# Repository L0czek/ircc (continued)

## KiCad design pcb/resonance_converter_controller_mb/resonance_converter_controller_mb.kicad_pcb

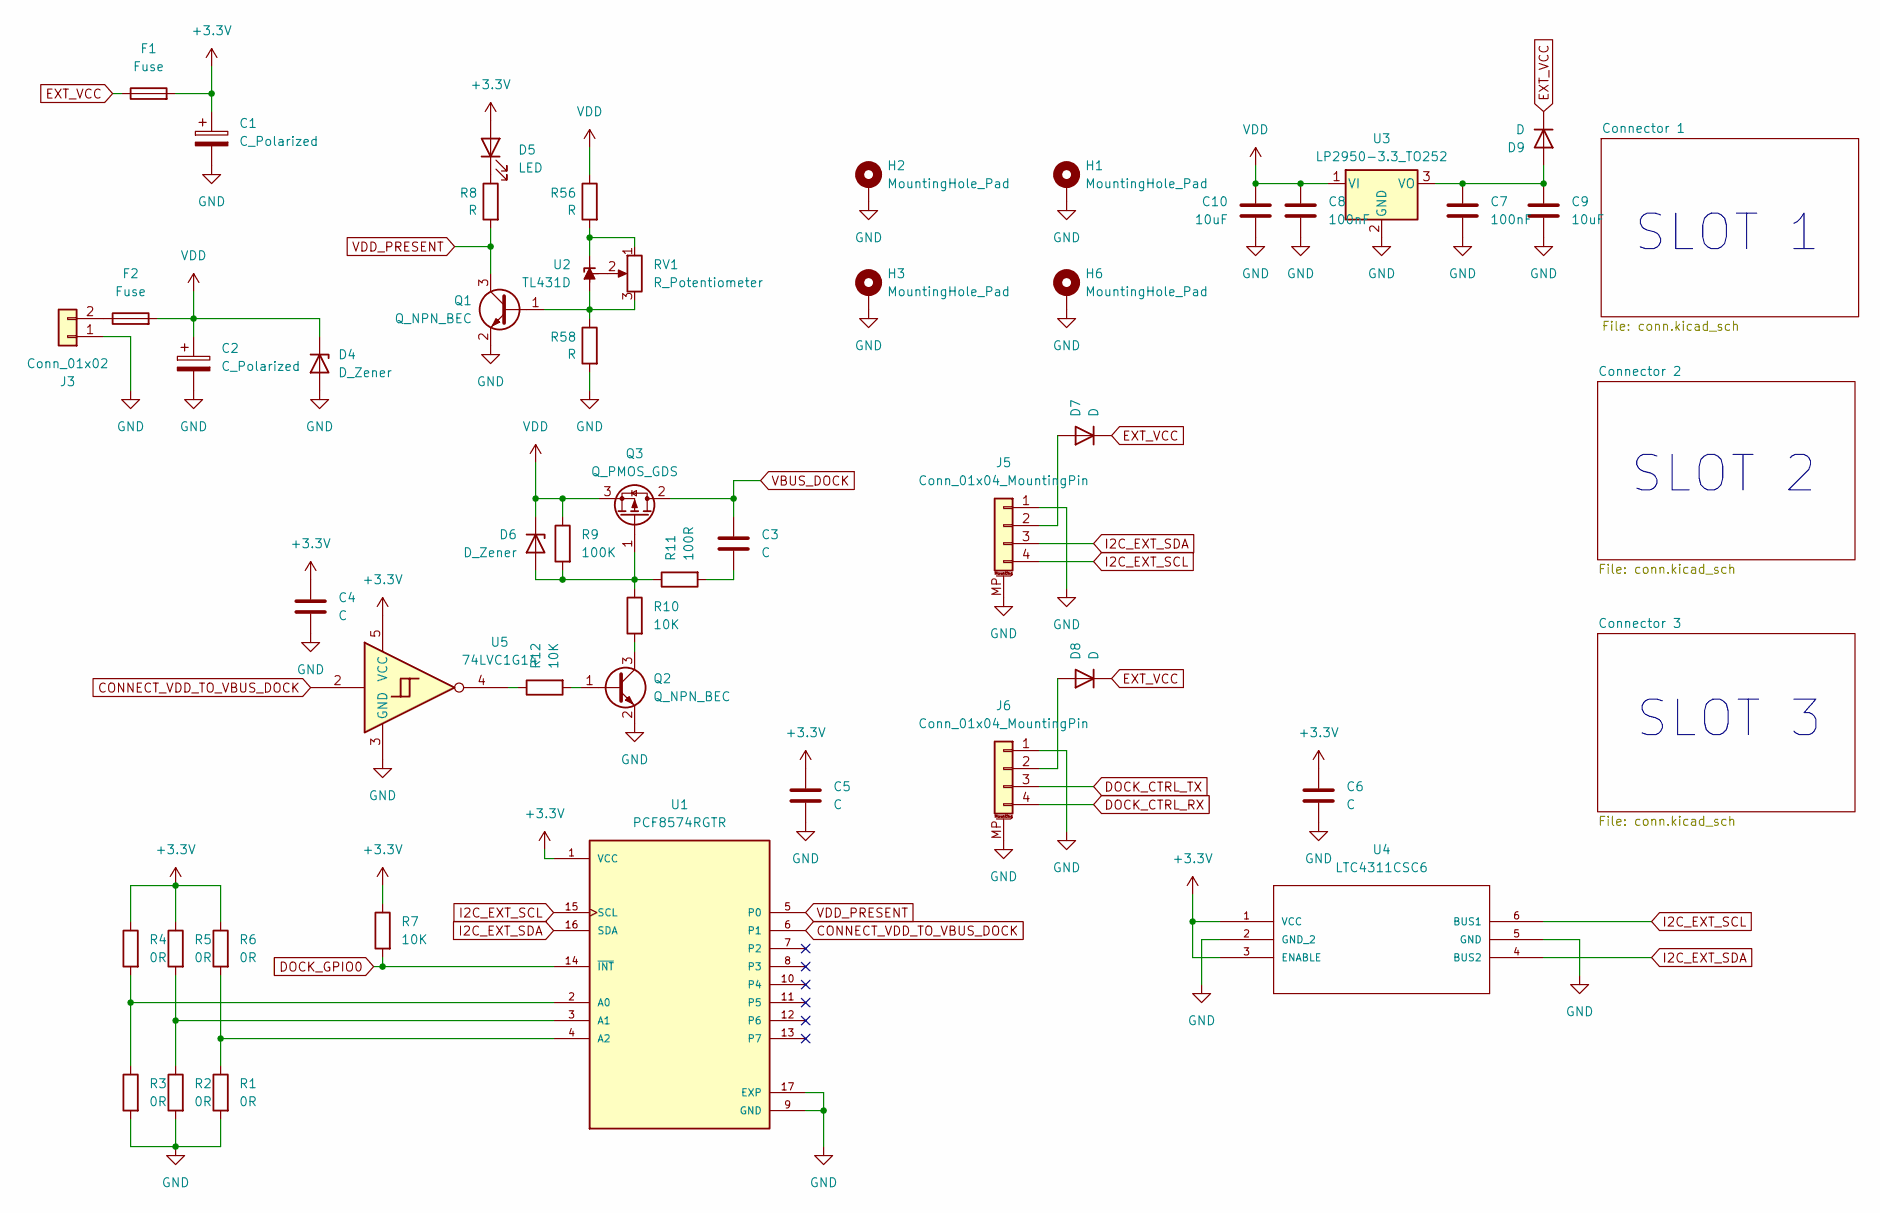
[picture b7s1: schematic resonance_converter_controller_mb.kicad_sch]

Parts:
C1, C2: C_Polarized; CP_Elec_10x10
C3, C4, C5, C6: C; C_0805_2012Metric
C7, C8: 100nF; C_0805_2012Metric
C9, C10: 10uF; C_0805_2012Metric
D4: D_Zener; D_SMC
D5: LED; LED_1206_3216Metric
D6: D_Zener; D_MiniMELF
D7, D8, D9: D; D_SMA
F1, F2: Fuse; Fuseholder_Clip-5x20mm_Keystone_3518P_Inline_P23.11x6.76mm_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
H1, H2, H3, H6: MountingHole_Pad; MountingHole_2.2mm_M2_Pad_Via
J3: Conn_01x02; AMASS_XT30PW-M_1x02_P2.50mm_Horizontal
J5, J6: Conn_01x04_MountingPin; JST_SH_SM04B-SRSS-TB_1x04-1MP_P1.00mm_Horizontal
Q1, Q2: Q_NPN_BEC; SOT-23
Q3: Q_PMOS_GDS; TO-263-2
R1, R2, R3, R4, R5, R6: 0R; R_0805_2012Metric
R7, R10, R12: 10K; R_0805_2012Metric
R8, R56, R58: R; R_0805_2012Metric
R9: 100K; R_0805_2012Metric
R11: 100R; R_0805_2012Metric
RV1: R_Potentiometer; Potentiometer_Bourns_3269W_Vertical
U1: PCF8574RGTR; QFN50P300X300X100-17N; PARTREV J; DigiKey_Part_Number 296-21238-1-ND
U2: TL431D; SOIC-8_3.9x4.9mm_P1.27mm
U3: LP2950-3.3_TO252; TO-252-2
U4: LTC4311CSC6; SC70-SC6; MANUFACTURER_PART_NUMBER ltc4311csc6#pbf
U5: 74LVC1G14

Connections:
+3.3V: C1.1, C4.1, C5.1, C6.1, D5.2 (A), F1.2, R4.1, R5.1, R6.1, R7.1, U1.1 (VCC), U4.1 (VCC), U4.3 (ENABLE), U5.5 (VCC); also elsewhere on the board
CONNECT_VDD_TO_VBUS_DOCK: U1.6 (P1), U5.2; also elsewhere on the board
DOCK_CTRL_RX: J6.4; also elsewhere on the board
DOCK_CTRL_TX: J6.3; also elsewhere on the board
DOCK_GPIO0: R7.2, U1.14 (~INT); also elsewhere on the board
EXT_VCC: D7.1 (K), D8.1 (K), D9.1 (K), F1.1; also elsewhere on the board
GND: C1.2, C2.2, C4.2, C5.2, C6.2, C7.2, C8.2, C9.2, C10.2, D4.2 (A), H1.1 (1_1), H2.1 (1_1), H3.1 (1_1), H6.1 (1_1), J3.1, J5.1, J5.MP (MountPin), J6.1, J6.MP (MountPin), Q1.2 (E), Q2.2 (E), R1.2, R2.2, R3.2, R58.2, U1.9 (GND), U1.17 (EXP), U3.2 (GND), U4.2 (GND_2), U4.5 (GND), U5.3 (GND); also elsewhere on the board
I2C_EXT_SCL: J5.4, U1.15 (SCL), U4.6 (BUS1); also elsewhere on the board
I2C_EXT_SDA: J5.3, U1.16 (SDA), U4.4 (BUS2); also elsewhere on the board
unnamed: C3.2, R11.2
unnamed: D5.1 (K), R8.1
unnamed: D6.2 (A), Q3.1 (G), R9.2, R10.1, R11.1
unnamed: D7.2 (A), J5.2
unnamed: D8.2 (A), J6.2
unnamed: C7.1, C9.1, D9.2 (A), U3.3 (VO)
unnamed: F2.1, J3.2
unnamed: Q1.1 (B), R58.1, RV1.3, U2.2 (A), U2.3 (A), U2.6 (A), U2.7 (A)
unnamed: Q2.1 (B), R12.2
unnamed: Q2.3 (C), R10.2
unnamed 53: R12.1, U5.4; also elsewhere on the board
unnamed: R3.1, R4.2, U1.2 (A0)
unnamed: R2.1, R5.2, U1.3 (A1)
unnamed: R1.1, R6.2, U1.4 (A2)
unnamed: R56.2, RV1.1, U2.1 (K)
unnamed: RV1.2, U2.8 (REF)
VBUS_DOCK: C3.1, Q3.2 (D); also elsewhere on the board
VDD: C2.1, C8.1, C10.1, D4.1 (K), D6.1 (K), F2.2, Q3.3 (S), R9.1, R56.1, U3.1 (VI)
VDD_PRESENT: Q1.3 (C), R8.2, U1.5 (P0)

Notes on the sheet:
SLOT 2
SLOT 3
SLOT 1

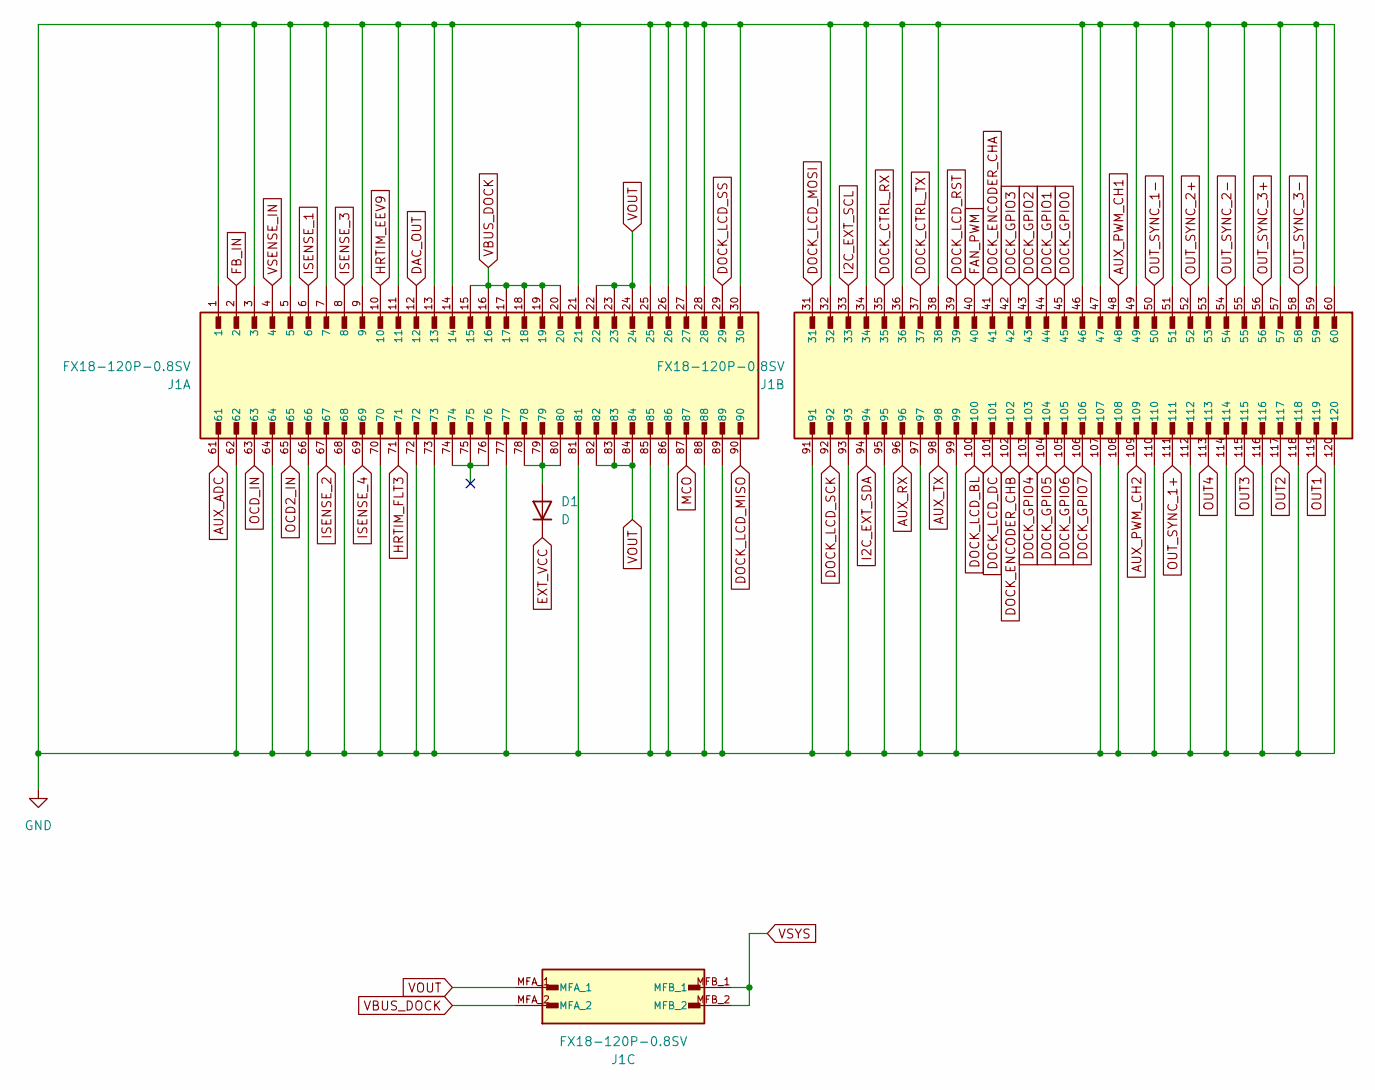
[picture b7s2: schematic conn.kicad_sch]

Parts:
D1: D; D_SMA
J1: FX18-120P-0.8SV; HIROSE_FX18-120P-0.8SV; PARTREV 11.07.21

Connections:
AUX_ADC: J1.61; also elsewhere on the board
AUX_PWM_CH1: J1.48; also elsewhere on the board
AUX_PWM_CH2: J1.109; also elsewhere on the board
AUX_RX: J1.96; also elsewhere on the board
AUX_TX: J1.98; also elsewhere on the board
DAC_OUT: J1.12; also elsewhere on the board
DOCK_CTRL_RX: J1.35; also elsewhere on the board
DOCK_CTRL_TX: J1.37; also elsewhere on the board
DOCK_ENCODER_CHA: J1.41; also elsewhere on the board
DOCK_ENCODER_CHB: J1.102; also elsewhere on the board
DOCK_GPIO0: J1.45; also elsewhere on the board
DOCK_GPIO1: J1.44; also elsewhere on the board
DOCK_GPIO2: J1.43; also elsewhere on the board
DOCK_GPIO3: J1.42; also elsewhere on the board
DOCK_GPIO4: J1.103; also elsewhere on the board
DOCK_GPIO5: J1.104; also elsewhere on the board
DOCK_GPIO6: J1.105; also elsewhere on the board
DOCK_GPIO7: J1.106; also elsewhere on the board
DOCK_LCD_BL: J1.100; also elsewhere on the board
DOCK_LCD_DC: J1.101; also elsewhere on the board
DOCK_LCD_MISO: J1.90; also elsewhere on the board
DOCK_LCD_MOSI: J1.31; also elsewhere on the board
DOCK_LCD_RST: J1.39; also elsewhere on the board
DOCK_LCD_SCK: J1.92; also elsewhere on the board
DOCK_LCD_SS: J1.29; also elsewhere on the board
EXT_VCC: D1.1 (K); also elsewhere on the board
FAN_PWM: J1.40; also elsewhere on the board
FB_IN: J1.2; also elsewhere on the board
GND: J1.1, J1.3, J1.5, J1.7, J1.9, J1.11, J1.13, J1.14, J1.21, J1.25, J1.26, J1.27, J1.28, J1.30, J1.32, J1.34, J1.36, J1.38, J1.46, J1.47, J1.49, J1.51, J1.53, J1.55, J1.57, J1.59, J1.60, J1.62, J1.64, J1.66, J1.68, J1.70, J1.72, J1.73, J1.77, J1.81, J1.85, J1.86, J1.88, J1.89, J1.91, J1.93, J1.95, J1.97, J1.99, J1.107, J1.108, J1.110, J1.112, J1.114, J1.116, J1.118, J1.120; also elsewhere on the board
HRTIM_EEV9: J1.10; also elsewhere on the board
HRTIM_FLT3: J1.71; also elsewhere on the board
I2C_EXT_SCL: J1.33; also elsewhere on the board
I2C_EXT_SDA: J1.94; also elsewhere on the board
ISENSE_1: J1.6; also elsewhere on the board
ISENSE_2: J1.67; also elsewhere on the board
ISENSE_3: J1.8; also elsewhere on the board
ISENSE_4: J1.69; also elsewhere on the board
MCO: J1.87; also elsewhere on the board
unnamed: D1.2 (A), J1.78, J1.79, J1.80
OCD2_IN: J1.65; also elsewhere on the board
OCD_IN: J1.63; also elsewhere on the board
OUT1: J1.119; also elsewhere on the board
OUT2: J1.117; also elsewhere on the board
OUT3: J1.115; also elsewhere on the board
OUT4: J1.113; also elsewhere on the board
OUT_SYNC_1+: J1.111; also elsewhere on the board
OUT_SYNC_1-: J1.50; also elsewhere on the board
OUT_SYNC_2+: J1.52; also elsewhere on the board
OUT_SYNC_2-: J1.54; also elsewhere on the board
OUT_SYNC_3+: J1.56; also elsewhere on the board
OUT_SYNC_3-: J1.58; also elsewhere on the board
VBUS_DOCK: J1.15, J1.16, J1.17, J1.18, J1.19, J1.20, J1.MFA_2; also elsewhere on the board
VOUT: J1.22, J1.23, J1.24, J1.82, J1.83, J1.84, J1.MFA_1; also elsewhere on the board
VSENSE_IN: J1.4; also elsewhere on the board
VSYS: J1.MFB_1, J1.MFB_2; also elsewhere on the board

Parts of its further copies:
D2, D3: D; D_SMA
J2, J4: FX18-120P-0.8SV; HIROSE_FX18-120P-0.8SV; PARTREV 11.07.21

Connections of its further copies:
AUX_ADC: J2.61, J4.61; also elsewhere on the board
AUX_PWM_CH1: J2.48, J4.48; also elsewhere on the board
AUX_PWM_CH2: J2.109, J4.109; also elsewhere on the board
AUX_RX: J2.96, J4.96; also elsewhere on the board
AUX_TX: J2.98, J4.98; also elsewhere on the board
DAC_OUT: J2.12, J4.12; also elsewhere on the board
DOCK_CTRL_RX: J2.35, J4.35; also elsewhere on the board
DOCK_CTRL_TX: J2.37, J4.37; also elsewhere on the board
DOCK_ENCODER_CHA: J2.41, J4.41; also elsewhere on the board
DOCK_ENCODER_CHB: J2.102, J4.102; also elsewhere on the board
DOCK_GPIO0: J2.45, J4.45; also elsewhere on the board
DOCK_GPIO1: J2.44, J4.44; also elsewhere on the board
DOCK_GPIO2: J2.43, J4.43; also elsewhere on the board
DOCK_GPIO3: J2.42, J4.42; also elsewhere on the board
DOCK_GPIO4: J2.103, J4.103; also elsewhere on the board
DOCK_GPIO5: J2.104, J4.104; also elsewhere on the board
DOCK_GPIO6: J2.105, J4.105; also elsewhere on the board
DOCK_GPIO7: J2.106, J4.106; also elsewhere on the board
DOCK_LCD_BL: J2.100, J4.100; also elsewhere on the board
DOCK_LCD_DC: J2.101, J4.101; also elsewhere on the board
DOCK_LCD_MISO: J2.90, J4.90; also elsewhere on the board
DOCK_LCD_MOSI: J2.31, J4.31; also elsewhere on the board
DOCK_LCD_RST: J2.39, J4.39; also elsewhere on the board
DOCK_LCD_SCK: J2.92, J4.92; also elsewhere on the board
DOCK_LCD_SS: J2.29, J4.29; also elsewhere on the board
EXT_VCC: D2.1 (K), D3.1 (K); also elsewhere on the board
FAN_PWM: J2.40, J4.40; also elsewhere on the board
FB_IN: J2.2, J4.2; also elsewhere on the board
GND: J2.1, J2.3, J2.5, J2.7, J2.9, J2.11, J2.13, J2.14, J2.21, J2.25, J2.26, J2.27, J2.28, J2.30, J2.32, J2.34, J2.36, J2.38, J2.46, J2.47, J2.49, J2.51, J2.53, J2.55, J2.57, J2.59, J2.60, J2.62, J2.64, J2.66, J2.68, J2.70, J2.72, J2.73, J2.77, J2.81, J2.85, J2.86, J2.88, J2.89, J2.91, J2.93, J2.95, J2.97, J2.99, J2.107, J2.108, J2.110, J2.112, J2.114, J2.116, J2.118, J2.120, J4.1, J4.3, J4.5, J4.7, J4.9, J4.11, J4.13, J4.14, J4.21, J4.25, J4.26, J4.27, J4.28, J4.30, J4.32, J4.34, J4.36, J4.38, J4.46, J4.47, J4.49, J4.51, J4.53, J4.55, J4.57, J4.59, J4.60, J4.62, J4.64, J4.66, J4.68, J4.70, J4.72, J4.73, J4.77, J4.81, J4.85, J4.86, J4.88, J4.89, J4.91, J4.93, J4.95, J4.97, J4.99, J4.107, J4.108, J4.110, J4.112, J4.114, J4.116, J4.118, J4.120; also elsewhere on the board
HRTIM_EEV9: J2.10, J4.10; also elsewhere on the board
HRTIM_FLT3: J2.71, J4.71; also elsewhere on the board
I2C_EXT_SCL: J2.33, J4.33; also elsewhere on the board
I2C_EXT_SDA: J2.94, J4.94; also elsewhere on the board
ISENSE_1: J2.6, J4.6; also elsewhere on the board
ISENSE_2: J2.67, J4.67; also elsewhere on the board
ISENSE_3: J2.8, J4.8; also elsewhere on the board
ISENSE_4: J2.69, J4.69; also elsewhere on the board
MCO: J2.87, J4.87; also elsewhere on the board
unnamed: D2.2 (A), J2.78, J2.79, J2.80
unnamed: D3.2 (A), J4.78, J4.79, J4.80
OCD2_IN: J2.65, J4.65; also elsewhere on the board
OCD_IN: J2.63, J4.63; also elsewhere on the board
OUT1: J2.119, J4.119; also elsewhere on the board
OUT2: J2.117, J4.117; also elsewhere on the board
OUT3: J2.115, J4.115; also elsewhere on the board
OUT4: J2.113, J4.113; also elsewhere on the board
OUT_SYNC_1+: J2.111, J4.111; also elsewhere on the board
OUT_SYNC_1-: J2.50, J4.50; also elsewhere on the board
OUT_SYNC_2+: J2.52, J4.52; also elsewhere on the board
OUT_SYNC_2-: J2.54, J4.54; also elsewhere on the board
OUT_SYNC_3+: J2.56, J4.56; also elsewhere on the board
OUT_SYNC_3-: J2.58, J4.58; also elsewhere on the board
VBUS_DOCK: J2.15, J2.16, J2.17, J2.18, J2.19, J2.20, J2.MFA_2, J4.15, J4.16, J4.17, J4.18, J4.19, J4.20, J4.MFA_2; also elsewhere on the board
VOUT: J2.22, J2.23, J2.24, J2.82, J2.83, J2.84, J2.MFA_1, J4.22, J4.23, J4.24, J4.82, J4.83, J4.84, J4.MFA_1; also elsewhere on the board
VSENSE_IN: J2.4, J4.4; also elsewhere on the board
VSYS: J2.MFB_1, J2.MFB_2, J4.MFB_1, J4.MFB_2; also elsewhere on the board

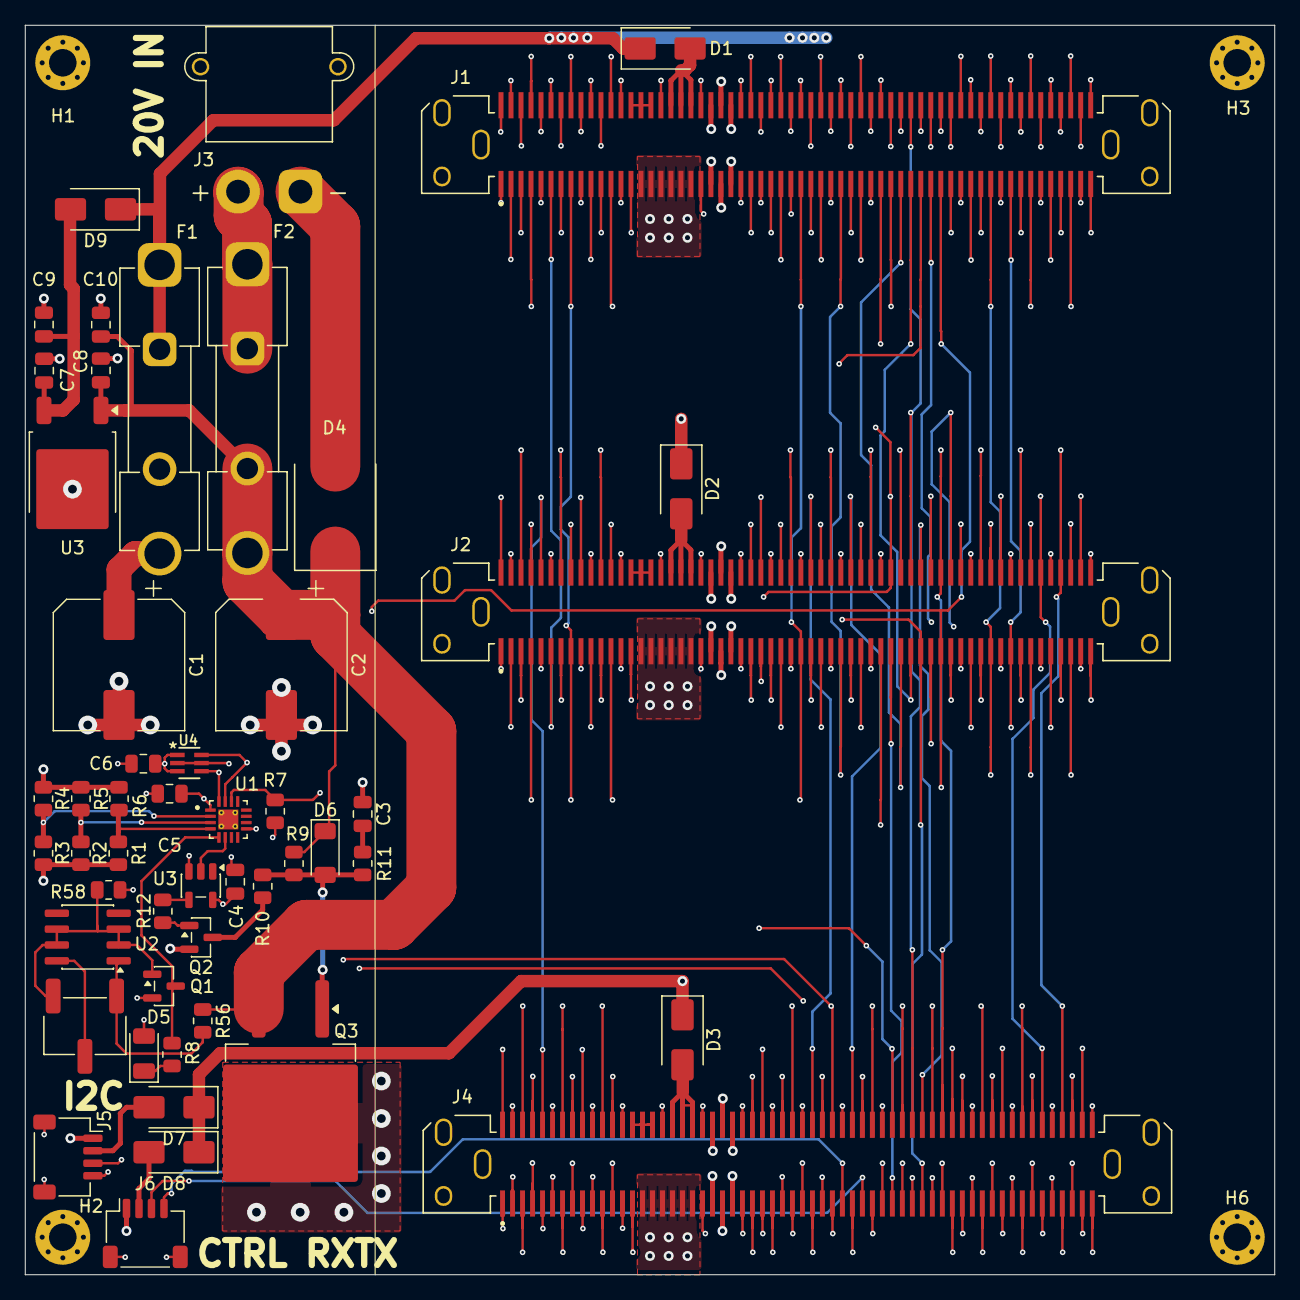
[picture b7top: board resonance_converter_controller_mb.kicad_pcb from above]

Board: 6 copper layers, 100.0 x 100.0 mm, 54 parts (0 on the bottom side), 77 nets.

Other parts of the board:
U3#2: 74LVC1G04; SOT-23-5

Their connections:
+3.3V: U3#2.5 (VCC); also elsewhere on the board
CONNECT_VDD_TO_VBUS_DOCK: U3#2.2; also elsewhere on the board
GND: U3#2.3 (GND); also elsewhere on the board
unnamed 53: U3#2.4; also elsewhere on the board

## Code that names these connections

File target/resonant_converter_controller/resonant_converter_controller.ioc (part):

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Mcu.Name=STM32G474V(B-C-E)Hx
Mcu.Package=TFBGA100
Mcu.UserName=STM32G474VEHx
PA0.Signal=S_TIM2_CH1
PA1.Signal=S_TIM2_CH2
PA10.Mode=Output_TB1
PA10.Signal=HRTIM1_CHB1
PA11.Mode=Device
PA11.Signal=USB_DM
PA12.Mode=Device
PA12.Signal=USB_DP
PA13.Mode=Serial_Wire
PA13.Signal=SYS_JTMS-SWDIO
PA14.Mode=Serial_Wire
PA14.Signal=SYS_JTCK-SWCLK
PA15.Mode=NSS_Signal_Hard_Output
PA15.Signal=SPI3_NSS
PA2.Mode=IN3-Single-Ended
PA2.Signal=ADC1_IN3
PA3.Signal=SharedAnalog_PA3
PA4.Signal=COMP_DAC11_group
PA5.Signal=COMP_DAC12_group
PA6.Signal=S_TIM3_CH1
PA7.Mode=IN4-Single-Ended
PA7.Signal=ADC2_IN4
PA8.Mode=I2C
PA8.Signal=I2C3_SCL
PA9.Mode=Output_TA2
PA9.Signal=HRTIM1_CHA2
PB1.Signal=SharedAnalog_PB1
PB10.Mode=Fault_Enable3
PB10.Signal=HRTIM1_FLT3
PB11.Signal=SharedAnalog_PB11
PB12.Mode=Output_TC1TC2
PB12.Signal=HRTIM1_CHC1
PB13.Mode=Output_TC1TC2
PB13.Signal=HRTIM1_CHC2
PB14.Mode=Output_TD1TD2
PB14.Signal=HRTIM1_CHD1
PB15.Mode=Output_TD1TD2
PB15.Signal=HRTIM1_CHD2
PB2.Signal=S_TIM20_CH1
PB3.Mode=External_Evt_enable9
PB3.Signal=HRTIM1_EEV9
PB4.Mode=Dual_Role_AllSignals
PB4.Signal=UCPD1_CC2
PB5.Mode=I2C
PB5.Signal=I2C3_SDA
PB6.Mode=Dual_Role_AllSignals
PB6.Signal=UCPD1_CC1
PB7.Signal=GPIO_Input
PB8-BOOT0.Mode=I2C
PB8-BOOT0.Signal=I2C1_SCL
PB9.Mode=I2C
PB9.Signal=I2C1_SDA
PC0.Signal=S_TIM1_CH1
PC1.Signal=SharedAnalog_PC1
PC10.Mode=Full_Duplex_Master
PC10.Signal=SPI3_SCK
PC11.Mode=Full_Duplex_Master
PC11.Signal=SPI3_MISO
PC12.Mode=Full_Duplex_Master
PC12.Signal=SPI3_MOSI
PC13.Signal=GPIO_Output
PC14-OSC32_IN.Signal=GPIO_Input
PC15-OSC32_OUT.Signal=GPIO_Output
PC2.Mode=Dual Bank
PC2.Signal=QUADSPI1_BK2_IO1
PC3.Mode=Dual Bank
PC3.Signal=QUADSPI1_BK2_IO2
PC4.Mode=IN5-Single-Ended
PC4.Signal=ADC2_IN5
PC5.Signal=GPIO_Input
PC6.Mode=Output_TF1TF2
PC6.Signal=HRTIM1_CHF1
PC7.Mode=Output_TF1TF2
PC7.Signal=HRTIM1_CHF2
PC8.Mode=Output_TE1TE2
PC8.Signal=HRTIM1_CHE1
PC9.Mode=Output_TE1TE2
PC9.Signal=HRTIM1_CHE2
PD0.Signal=GPIO_Output
PD1.Signal=GPIO_Output
PD10.Signal=GPIO_Output
PD12.Signal=SharedAnalog_PD12
PD13.Signal=GPIO_Output
PD15.Signal=GPIO_Output
PD2.Signal=GPIO_Output
PD3.Mode=Enable Chip Select 2 for both banks
PD3.Signal=QUADSPI1_BK2_NCS
PD4.Mode=Dual Bank
PD4.Signal=QUADSPI1_BK2_IO0
PD5.Mode=Asynchronous
PD5.Signal=USART2_TX
PD6.Mode=Asynchronous
PD6.Signal=USART2_RX
PD7.Mode=Dual Bank
PD7.Signal=QUADSPI1_BK2_IO3
PD8.Signal=GPIO_Output
PD9.Signal=GPIO_Output
PE0.Mode=Asynchronous
PE0.Signal=USART1_TX
PE1.Mode=Asynchronous
PE1.Signal=USART1_RX
PE10.Signal=GPIO_Output
PE11.Signal=GPIO_Output
PE12.Mode=Dual Bank
PE12.Signal=QUADSPI1_BK1_IO0
PE14.Mode=Dual Bank
PE14.Signal=QUADSPI1_BK1_IO2
PE15.Mode=Dual Bank
PE15.Signal=QUADSPI1_BK1_IO3
PE2.Mode=Full_Duplex_Master
PE2.Signal=SPI4_SCK
PE3.Signal=S_TIM20_CH2
PE4.Mode=NSS_Signal_Hard_Output
PE4.Signal=SPI4_NSS
PE5.Mode=Full_Duplex_Master
PE5.Signal=SPI4_MISO
PE6.Mode=Full_Duplex_Master
PE6.Signal=SPI4_MOSI
PE7.Signal=SharedAnalog_PE7
PE8.Signal=GPIO_Output
PE9.Signal=S_TIM5_CH4
PF0-OSC_IN.Mode=HSE-External-Oscillator
PF0-OSC_IN.Signal=RCC_OSC_IN
PF1-OSC_OUT.Mode=HSE-External-Oscillator
PF1-OSC_OUT.Signal=RCC_OSC_OUT
PF10.Mode=Dual Bank
PF10.Signal=QUADSPI1_CLK
PF9.Mode=Dual Bank
PF9.Signal=QUADSPI1_BK1_IO1
PG10-NRST.Mode=Clock-out
PG10-NRST.Signal=RCC_MCO
RCC.HSE_VALUE=25000000
RCC.SYSCLKFreq_VALUE=170000000
RCC.SYSCLKSource=RCC_SYSCLKSOURCE_PLLCLK
board=custom

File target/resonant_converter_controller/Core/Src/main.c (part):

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GPIO_pin_t g_board_vout_enable = {
    .GPIOx = GPIOC, .pin = GPIO_PIN_15
};
/* PC13 = BRIDGE_VOUT_VBUS_USB: high enables U26 (TPS259474A eFuse, VOUT -> VBUS_USBC,
   3 A limit, reverse blocking). 10 k pull-down: off at reset. Driven by PowerPath. */
GPIO_pin_t g_board_usb_vout_bridge = {
    .GPIOx = GPIOC, .pin = GPIO_PIN_13
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GPIO_pin_t g_board_lcd_bl = {
    .GPIOx = GPIOD, .pin = GPIO_PIN_0
};
/* PD0 is the USB_DEAD_BATT_DISABLE net (there is no LCD backlight net; the CubeMX label is
   stale): low keeps the external dead-battery Rd on CC1/CC2. Driven by USBPD_DPM_UserInit. */
GPIO_pin_t g_board_usb_dead_batt_disable = {
    .GPIOx = GPIOD, .pin = GPIO_PIN_0
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GPIO_pin_t g_board_lcd_rst = {
    .GPIOx = GPIOD, .pin = GPIO_PIN_2
};
/* PA15 = LCD_SS (SSD1327 CS#), driven as a GPIO once CubeMX sets it to GPIO_Output
   (docs/lcd_ui.md); while it is still SPI3_NSS the hardware drives it. */
GPIO_pin_t g_board_lcd_cs = {
    .GPIOx = GPIOA, .pin = GPIO_PIN_15
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
  LL_AHB2_GRP1_EnableClock(LL_AHB2_GRP1_PERIPH_GPIOB);
  /**UCPD1 GPIO Configuration
  PB6   ------> UCPD1_CC1
  PB4   ------> UCPD1_CC2
  */
  GPIO_InitStruct.Pin = LL_GPIO_PIN_6;
  GPIO_InitStruct.Mode = LL_GPIO_MODE_ANALOG;
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  /*Configure GPIO pin Output Level */
  HAL_GPIO_WritePin(GPIOE, GPIO_PIN_8|GPIO_PIN_11|GPIO_PIN_10, GPIO_PIN_RESET);

  /*Configure GPIO pins : PD1 PD2 PD0 PD10
                           PD9 PD13 PD15 PD8 */
  GPIO_InitStruct.Pin = GPIO_PIN_1|GPIO_PIN_2|GPIO_PIN_0|GPIO_PIN_10
                          |GPIO_PIN_9|GPIO_PIN_13|GPIO_PIN_15|GPIO_PIN_8;
  GPIO_InitStruct.Mode = GPIO_MODE_OUTPUT_PP;
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  GPIO_InitStruct.Speed = GPIO_SPEED_FREQ_LOW;
  HAL_GPIO_Init(GPIOD, &GPIO_InitStruct);

  /*Configure GPIO pin : PB7 */
  GPIO_InitStruct.Pin = GPIO_PIN_7;
  GPIO_InitStruct.Mode = GPIO_MODE_INPUT;
  GPIO_InitStruct.Pull = GPIO_NOPULL;
  HAL_GPIO_Init(GPIOB, &GPIO_InitStruct);

  /*Configure GPIO pins : PC14 PC5 */
  GPIO_InitStruct.Pin = GPIO_PIN_14|GPIO_PIN_5;
  GPIO_InitStruct.Mode = GPIO_MODE_INPUT;
  GPIO_InitStruct.Pull = GPIO_NOPULL;
  HAL_GPIO_Init(GPIOC, &GPIO_InitStruct);

  /*Configure GPIO pins : PC15 PC13 */
  GPIO_InitStruct.Pin = GPIO_PIN_15|GPIO_PIN_13;
  GPIO_InitStruct.Mode = GPIO_MODE_OUTPUT_PP;
  GPIO_InitStruct.Pull = GPIO_NOPULL;
  GPIO_InitStruct.Speed = GPIO_SPEED_FREQ_LOW;
  HAL_GPIO_Init(GPIOC, &GPIO_InitStruct);

  /*Configure GPIO pin : PG10 */
  GPIO_InitStruct.Pin = GPIO_PIN_10;
  GPIO_InitStruct.Mode = GPIO_MODE_AF_PP;
  GPIO_InitStruct.Pull = GPIO_NOPULL;
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  GPIO_InitStruct.Alternate = GPIO_AF0_MCO;
  HAL_GPIO_Init(GPIOG, &GPIO_InitStruct);

  /*Configure GPIO pins : PE8 PE11 PE10 */
  GPIO_InitStruct.Pin = GPIO_PIN_8|GPIO_PIN_11|GPIO_PIN_10;
  GPIO_InitStruct.Mode = GPIO_MODE_OUTPUT_PP;
  GPIO_InitStruct.Pull = GPIO_NOPULL;
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
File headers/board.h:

#ifndef __BOARD_H__
#define __BOARD_H__

#include "stm32g4xx_hal.h"
#include "stm32g4xx_hal_dac.h"
#include "stm32g4xx_hal_adc.h"
#include "stm32g4xx_hal_crc.h"
#include "stm32g4xx_hal_dma.h"
#include "stm32g4xx_hal_i2c.h"
#include "stm32g4xx_hal_uart.h"
#include "stm32g4xx_hal_tim.h"
#include "stm32g4xx_hal_hrtim.h"
#include "stm32g4xx_hal_spi.h"
#include "stm32g4xx_hal_qspi.h"

#ifdef __cplusplus

extern "C" {

#endif

typedef struct {
    GPIO_TypeDef* GPIOx;
    uint32_t pin;
} GPIO_pin_t;

typedef struct {
    DAC_HandleTypeDef *DACx;
    uint32_t channel;
} DAC_channel_t;

typedef struct {
    ADC_HandleTypeDef *ADCx;
    uint32_t channel;
} ADC_channel_t;

// Board peripheral externs - names imported from target/resonant_converter_controller/Core/Src/main.c
#if defined(stm32g474re_nucleo_board)
// Nucleo board - use g_board_* naming directly
extern TIM_HandleTypeDef *g_board_tim_feedback;
extern TIM_HandleTypeDef *g_board_tim_debug;
extern HRTIM_HandleTypeDef *g_board_hrtim;
extern I2C_HandleTypeDef *g_board_i2c_internal;
extern UART_HandleTypeDef *g_board_ctl_uart;
extern DMA_HandleTypeDef *g_board_dma_uart_rx;
extern DMA_HandleTypeDef *g_board_dma_uart_tx;
extern CRC_HandleTypeDef *g_board_crc32;
extern DAC_HandleTypeDef *g_board_dac_ch1;
extern DAC_HandleTypeDef *g_board_dac_ch2;
extern DAC_HandleTypeDef *g_board_dac_ch3;
extern DAC_HandleTypeDef *g_board_dac_ch4;
extern DAC_HandleTypeDef *g_board_dac_channels[4];
// Channel aliases for aux_pwm timer (TIM_DEBUG)
#define g_board_aux_pwm g_board_tim_debug
#define g_board_aux_pwm_cha TIM_CHANNEL_1
#define g_board_aux_pwm_chb TIM_CHANNEL_2
#elif defined(resonant_converter_controller)
// Resonant converter controller - use g_board_* naming from main.c
extern HRTIM_HandleTypeDef *g_board_hrtim;
extern TIM_HandleTypeDef *g_board_tim_feedback;
extern TIM_HandleTypeDef *g_board_aux_pwm;
extern const uint32_t g_board_aux_pwm_cha;
extern const uint32_t g_board_aux_pwm_chb;
extern TIM_HandleTypeDef *g_board_tim_fan_pwm;
extern TIM_HandleTypeDef *g_board_tim_ws2812b;
extern TIM_HandleTypeDef *g_board_tim_encoder;
extern I2C_HandleTypeDef *g_board_i2c_internal;
extern I2C_HandleTypeDef *g_board_i2c_external;
extern SPI_HandleTypeDef *g_board_lcd_spi;
extern SPI_HandleTypeDef *g_board_sdcard_spi;
extern QSPI_HandleTypeDef *g_board_psram_qspi;
extern TIM_HandleTypeDef *g_board_tim_adc_trgo;      // oscilloscope sample timer (TIM8)
extern UART_HandleTypeDef *g_board_ctl_uart;
extern UART_HandleTypeDef *g_board_aux_uart;
extern CRC_HandleTypeDef *g_board_crc32;
extern DAC_HandleTypeDef *g_board_dac_ch1;
extern DAC_HandleTypeDef *g_board_dac_ch2;
extern DAC_HandleTypeDef *g_board_dac_ch3;
extern DAC_HandleTypeDef *g_board_dac_ch4;
extern DAC_HandleTypeDef *g_board_dac_channels[4];

// Timer channels / HRTIM resources (defined next to the handles in main.c)
extern const uint32_t g_board_hrtim_out1;
extern const uint32_t g_board_hrtim_out2;
extern const uint32_t g_board_hrtim_out3;
extern const uint32_t g_board_hrtim_out4;
extern const uint32_t g_board_hrtim_sync_out1_p;
extern const uint32_t g_board_hrtim_sync_out1_n;
extern const uint32_t g_board_hrtim_sync_out2_p;
extern const uint32_t g_board_hrtim_sync_out2_n;
extern const uint32_t g_board_hrtim_sync_out3_p;
extern const uint32_t g_board_hrtim_sync_out3_n;
extern const uint32_t g_board_hrtim_delayd_eev1;
extern const uint32_t g_board_hrtim_flt;
extern const uint32_t g_board_tim_feedback_channel;
extern const uint32_t g_board_tim_fan_pwm_channel;      // TIM3_CH1, PA6 -> FAN_PWM (dock 4-pin fan)
extern const uint32_t g_board_tim_ws2812b_channel;      // TIM5_CH4, PE9 -> WS2812B DIN

// Analog front end
extern DAC_channel_t g_board_fb_sync_v;
extern DAC_channel_t g_board_dac_aux_v;
extern DAC_channel_t g_board_fb_ocd_comp_v;
extern DAC_channel_t g_board_fb_ocd2_comp_v;
extern DAC_channel_t g_board_isense_comp_v[4];
extern ADC_channel_t g_board_aux_adc_read_v;
extern ADC_channel_t g_board_dac_aux_read_back_v;
extern ADC_channel_t g_board_fb_ocd_read_v;
extern ADC_channel_t g_board_fb_ocd2_read_v;
extern ADC_channel_t g_board_vsense_read_v;
extern COMP_HandleTypeDef *g_board_isense[4];
extern COMP_HandleTypeDef *g_board_fb_ocd;
extern COMP_HandleTypeDef *g_board_fb_ocd2;

// GPIOs
extern GPIO_pin_t g_board_gpios[8];
extern GPIO_pin_t g_board_power_int;
extern GPIO_pin_t g_board_vout_enable;
extern GPIO_pin_t g_board_sdcard_detect;
extern GPIO_pin_t g_board_mco_nrst_sel;
extern GPIO_pin_t g_board_usb_dap_en;
extern GPIO_pin_t g_board_usb_dap_dir;
extern GPIO_pin_t g_board_lcd_bl;
extern GPIO_pin_t g_board_lcd_dc;
extern GPIO_pin_t g_board_lcd_rst;
extern GPIO_pin_t g_board_lcd_cs;     // PA15 LCD_SS (SSD1327 CS#)
extern GPIO_pin_t g_board_key_int;
// PD0 = USB_DEAD_BATT_DISABLE (high disconnects the external dead-battery Rd on CC1/CC2);
// g_board_lcd_bl is the same pin under its stale CubeMX name.
extern GPIO_pin_t g_board_usb_dead_batt_disable;
// PC13 = BRIDGE_VOUT_VBUS_USB: high connects VOUT to the USB-C VBUS (U26 eFuse)
extern GPIO_pin_t g_board_usb_vout_bridge;
#endif

// BOARD_CONFIG struct for use in C++ code
// This must be defined AFTER the extern declarations so we can reference HAL types
struct BoardConfig {
    UART_HandleTypeDef* message_bus;
    CRC_HandleTypeDef* crc32;
};

// BOARD_CONFIG instance - defined in main.c
#if defined(stm32g474re_nucleo_board) || defined(resonant_converter_controller)
extern struct BoardConfig g_board_config;
#define BOARD_CONFIG g_board_config
#endif

void controller_system_init(void);

#ifdef __cplusplus

}

#endif

#endif

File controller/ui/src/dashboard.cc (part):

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    }

    void draw_footer(Ui& ui, Canvas& c, const Rect& footer) noexcept override {
        static const char* const kNames[] = {"Overview", "Charger", "VOUT", "USB-C", "Trends", "Applet"};
        c.text(footer.x + 1, footer.y + 1, kNames[page_], kFontSmall, gray::kLabel);
        const int pages = ui.running_applet() >= 0 ? PageCount : PageCount - 1;
        draw_dots(c, Rect{60, footer.y, 68, footer.h}, pages, page_);
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                    append(buf, sizeof(buf), tmp);
                }
            }
            draw_kv(c, y, "VOUT", buf, on ? gray::kValue : gray::kLabel);
            y += kLine;
        }

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            append(buf, sizeof(buf), tmp);
            format_value(tmp, sizeof(tmp), cfg.has_output_current_limit ? cfg.output_current_limit : NAN, 2, "A");
            append(buf, sizeof(buf), tmp);
            c.text(Rect{0, static_cast<int16_t>(y), kWidth, 10}, buf, kFontSmall, gray::kLabel, Align::Center);
        }
        y += 9;
        if (st.fault_present) {
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    void draw(Ui& ui, Canvas& c, const Rect& body) noexcept override {
        (void)body;
        const uint8_t keys = ui.key_tracker().pressed();
        c.text(Rect{0, 0, kWidth, 10}, "Input test", kFontBody, gray::kLabel, Align::Center);
        auto box = [&](int x, int y, Key k, const char* label) {
            const bool on = keys & key_bit(k);
            const Rect r{static_cast<int16_t>(x), static_cast<int16_t>(y), 16, 14};
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            } else {
                c.frame(r, gray::kLabel);
            }
            c.text(r, label, kFontSmall, on ? gray::kOff : gray::kLabel, Align::Center);
        };
        // Joystick cross
        box(24, 16, Key::Up, "U");
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
        if (have_last_) {
            static const char* const kTypes[] = {"press", "release", "click", "long", "repeat", "turn"};
            static const char* const kKeys[] = {"up", "down", "left", "right", "centre", "push", "shutdown", ""};
            std::strcpy(buf, kTypes[static_cast<int>(last_.type)]);
            append(buf, sizeof(buf), " ");
            if (last_.type == EventType::Turn) {
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                for (int g = 0; g < 16; ++g) {
                    c.fill(Rect{static_cast<int16_t>(g * 8), 0, 8, 112}, static_cast<Gray>(g));
                }
                c.text(Rect{0, 116, kWidth, 10}, "gray 0..15", kFontSmall, gray::kLabel, Align::Center);
                break;
            case 1:   // orientation: corners, arrow up, left/right pixel pair
                c.frame(Rect{0, 0, kWidth, kHeight}, gray::kValue);
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                c.line(64, 30, 64, 98, gray::kValue);
                c.line(64, 30, 50, 44, gray::kValue);
                c.line(64, 30, 78, 44, gray::kValue);
                c.text(Rect{0, 100, kWidth, 10}, "UP  (tail at bottom)", kFontSmall, gray::kLabel, Align::Center);
                // A bright pixel left of a dark one in every pair: shows a nibble swap
                for (int x = 20; x < 108; x += 4) {
                    c.pixel(x, 60, gray::kValue);
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
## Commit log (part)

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2025-06-13 Initial commit with target for stm32g4 nucleo board
2025-06-13 Connect boards with controller
2025-06-13 Add linking of compile_commands.json
2025-06-13 Add RTOS
2025-06-17 Add simple C++ layer to the cmsis rtos v2
2025-06-17 Add main task boiler plate
2025-06-17 Update nucleo board target
2025-06-17 Fix build system include directories
2025-06-17 Add global config file
2025-06-27 [WIP] add feedback input capture
2025-08-01 Start implementing HRTIM and add i2c scanner for testing
2025-09-02 Add error type
2025-09-02 Add dependencies as submodules
2025-09-02 Switch to C++23
2025-09-02 Integrate sfpconv with the build system
2025-09-03 Switch to another si5351lib
2025-09-13 Fix build system to use the new periph lib
2025-09-13 Update dependencies
2025-11-15 Update submodules
2025-11-15 Add host part with protocol
2025-11-15 Switch to normal pointers as it is not rust :(
2025-11-17 Fix compilation bug in queue
2025-11-17 Edit target, add CRC32 and UART
2025-11-17 Start implementing message handling
2025-11-22 Add message habdling for the target
2025-11-22 Add host utility with tui and message handling
2025-11-25 Fix a lot of bugs
2026-01-13 Start creating pcb for the controller
2026-01-13 Add CubeMX project for the pcb
2026-01-13 Add README
2026-03-21 Finish first schematic resivion of the SOM
2026-03-21 Fix typo
2026-03-23 Create first version of the dock
2026-03-23 Update conector in dock
2026-03-23 Update conector in som
2026-03-23 Cleanup
2026-03-25 Fix errors and make initial component placement in dock
2026-03-28 First routing without testpoints
2026-03-29 Add mounting holes and some rework
2026-04-02 Add reset handler buffer for dac and led
2026-04-06 Add io panel and fix controller pcb
2026-05-07 Add digital pots to auto adjust gain
2026-05-07 Add debug probe idea based on osd32mp1
2026-05-07 Add motherboard preview
2026-05-08 Prep for autoroute
2026-05-16 Prep connector board for autoroute
2026-05-17 Add schematic for debug probe
2026-05-19 _mb board freerouted
2026-05-19 Add I2C line terminator
2026-05-20 connctor board routed
2026-05-20 Fix silkscreen
2026-05-20 Reduce copper layers as it fits on 4
2026-05-20 Kicad 9 -> 10
2026-05-20 Fix schematic and initial component layout
2026-05-21 Add 3.3v regulator and fix silkscreen
2026-05-21 Reroute USB fix silkscreen and Kicad 9 -> 10
2026-05-21 Add 3rd row of output connectors
